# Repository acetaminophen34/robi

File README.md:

# Robi Development Project

ロボット「ロビ」の制御システムを開発・実験するためのプロジェクトです。

ESP32を用いたサーボモーター制御、Pythonによる操作GUI・モーション編集、Jetsonを用いた認識処理、制御基板の設計などを扱います。

## 使い方を探す

| やりたいこと | 案内 |
|---|---|
| ロビと対話し、モーションを実行する | [Jetson実機環境・起動方法](jetson/README.md) |
| ロビとテキストで会話する | [LLM対話の環境・起動方法](jetson/llm/README.md#起動) |
| どのプログラムを使うか確認する | [LLMファイルの役割](jetson/llm/README.md#ファイルの役割) |
| 口調・返答・モーション選択を調整する | [LLM対話の設定](jetson/llm/README.md#設定) |
| 起動や推論のエラーを調べる | [困ったとき](jetson/llm/README.md#困ったとき) |
| Jetsonへコードを反映する | [GitHub経由](jetson/llm/README.md#github経由のデプロイ)・[SSH/SCP経由](jetson/llm/README.md#macからsshscpで今回の差分を試す) |
| モーションを編集・再生する | [モーションエディタの使い方](motion_editor/README.md) |
| JetsonからUSB経由でRobiに接続する | [ESP32とのシリアル接続メモ](jetson/serial_connection.md) |
| Jetsonの推論環境を準備する | [jetson-labの環境構築](https://github.com/acetaminophen34/jetson-lab)・[llama-serverの追加ビルド](https://github.com/acetaminophen34/jetson-lab/blob/main/llama-cpp/server.md) |

Jetsonでの対話＋モーション制御は[実機環境・起動方法](jetson/README.md)を参照してください。テキスト対話のみの場合は`jetson/llm/chat.py`から起動します。サーバーの導入・ビルドはjetson-lab、対話の使い方・設定はこのリポジトリで管理しています。

## ディレクトリ構成

| ディレクトリ | 内容 |
|---|---|
| `esp/` | ESP32向けプログラムおよびPython GUI |
| `esp/gui_motion/` | モーション編集・制御の試作とテスト |
| `esp/head/` | 頭部のサーボ・LEDなどの制御 |
| `esp/servo/` | サーボモーターの動作確認 |
| `motion_editor/` | モーション作成・編集・再生用のPythonツール |
| `jetson/llm/` | Qwen3常駐サーバーによるテキスト対話・モーション選択（[手順](jetson/llm/README.md)） |
| `jetson/classification/` | Jetson向けの分類処理 |
| `robi_PCB/` | KiCadによる制御基板の設計データ |

## 開発環境

使用する技術・ツール：

- Python
- Arduino / ESP32
- NVIDIA Jetson
- KiCad
- Visual Studio Code

Pythonプログラムの依存パッケージは、各ディレクトリの`requirements.txt`を参照してください。

## モーションデータ

モーションはJSON形式で管理しています。

`motion_editor/motions/`にモーションデータを配置し、編集・再生ツールから利用します。

データ形式や操作方法の詳細は、各ツールのREADMEを参照してください。

## Git管理について

本リポジトリでは、開発用のソースコード・設定ファイル・基板設計データを管理します。

仮想環境、ビルド生成物、一時ファイル、KiCadの自動バックアップなどは原則として管理対象外です。

また、一部の既存ソフトウェア・関連データは権利関係の確認が必要なため、本リポジトリには含めていません。

## 開発状況

開発・実験中のプロジェクトです。各機能の仕様や構成は変更される場合があります。

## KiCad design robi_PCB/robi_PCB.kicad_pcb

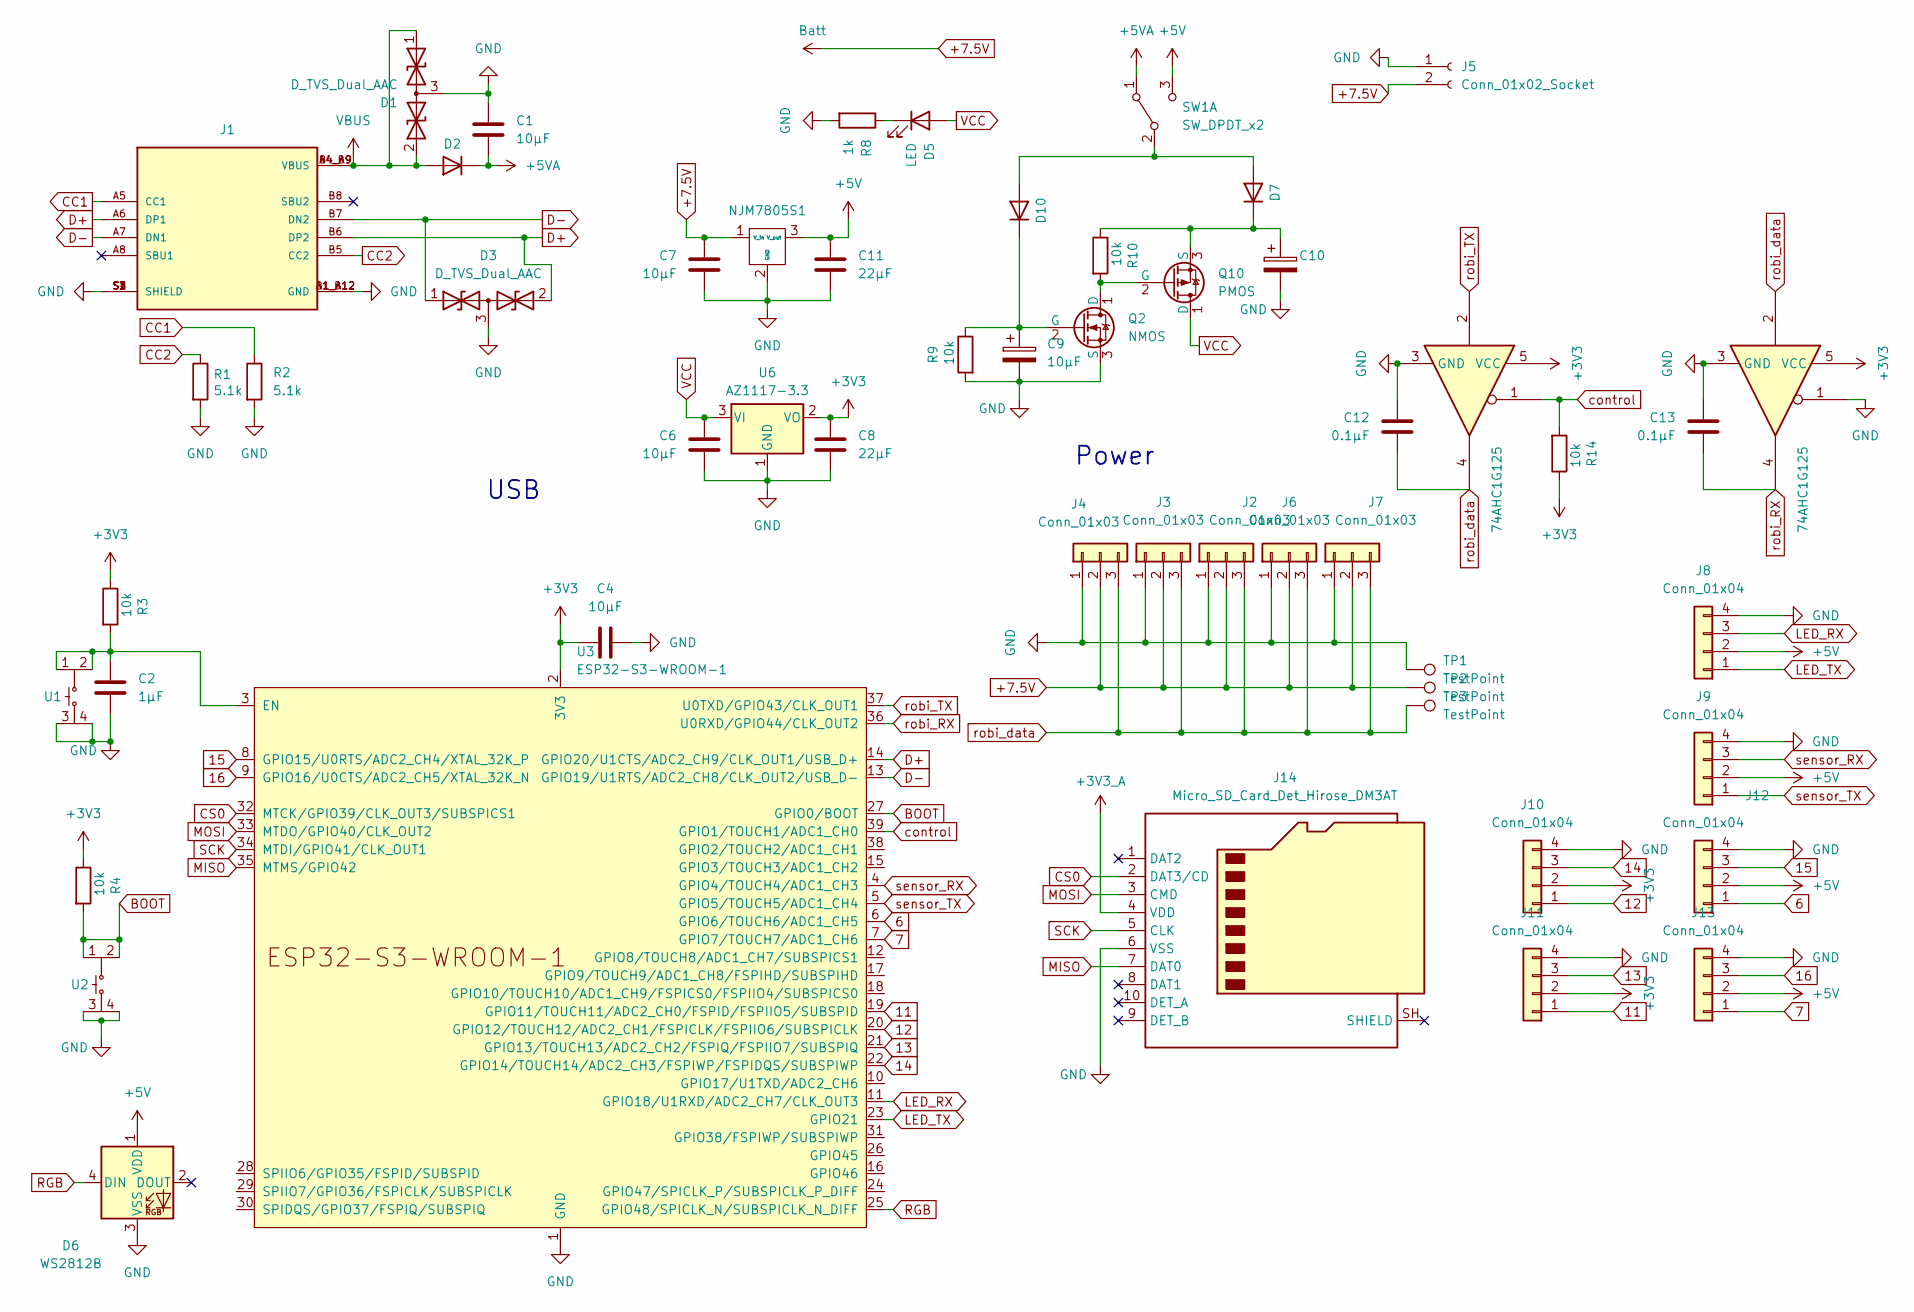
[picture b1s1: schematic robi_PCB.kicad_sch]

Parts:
C1, C4, C6, C7: 10μF; C_0805_2012Metric
C2: 1μF; C_0603_1608Metric
C8, C11: 22μF; C_0805_2012Metric
C9: 10μF; C_1206_3216Metric
C10: C_Polarized; CP_Radial_D8.0mm_P3.50mm
C12, C13: 0.1μF; C_0805_2012Metric
D1, D3: D_TVS_Dual_AAC; SOT-23
D2, D7, D10: D; D_SOD-323_HandSoldering
D5: LED; LED_0603_1608Metric
D6: WS2812B; LED_WS2812B_PLCC4_5.0x5.0mm_P3.2mm
J1: 5077CR-16SMC2-BK-TR; USB-C_SMT; PARTREV B
J2, J3, J4, J6, J7: Conn_01x03; JST_PH_B3B-PH-K_1x03_P2.00mm_Vertical
J5: Conn_01x02_Socket; JST_XH_B2B-XH-A_1x02_P2.50mm_Vertical
J8: Conn_01x04; JST_PH_B4B-PH-K_1x04_P2.00mm_Vertical
J9, J10, J11, J12, J13: Conn_01x04; PinHeader_1x04_P2.54mm_Vertical
J14: Micro_SD_Card_Det_Hirose_DM3AT; microSD_HC_Hirose_DM3AT-SF-PEJM5
NJM7805S1: NJM7805SDL1
Q2: NMOS; NMOS_IRLML6344TRPBFTR
Q10: PMOS; PMOS_AO3401A
R1, R2: 5.1k; R_0805_2012Metric
R3, R4, R9, R10, R14: 10k; R_0805_2012Metric
R8: 1k; R_0805_2012Metric
SW1: SW_DPDT_x2; SS-12D00G3
TP1, TP2, TP3: TestPoint; TestPoint_THTPad_1.0x1.0mm_Drill0.5mm
U1, U2: SKRPABE010
U3: ESP32-S3-WROOM-1
U4, U5: 74AHC1G125; SOT-23-5
U6: AZ1117-3.3; SOT-223-3_TabPin2

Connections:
6: J12.1, U3.6 (GPIO6/TOUCH6/ADC1_CH5)
7: J13.1, U3.7 (GPIO7/TOUCH7/ADC1_CH6)
11: J11.1, U3.19 (GPIO11/TOUCH11/ADC2_CH0/FSPID/FSPIIO5/S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)
12: J10.1, U3.20 (GPIO12/TOUCH12/ADC2_CH1/FSPICLK/FSPIIO6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)
13: J11.3, U3.21 (GPIO13/TOUCH13/ADC2_CH2/FSPIQ/FSPIIO7/S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)
14: J10.3, U3.22 (GPIO14/TOUCH14/ADC2_CH3/FSPIWP/FSPIDQS/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)
15: J12.3, U3.8 (GPIO15/U0RTS/ADC2_CH4/XTAL_32K_P)
16: J13.3, U3.9 (GPIO16/U0CTS/ADC2_CH5/XTAL_32K_N)
+3V3: C4.1, C8.1, J10.2, J11.2, R3.1, R4.1, R14.1, U3.2 (3V3), U4.5 (VCC), U5.5 (VCC), U6.2 (VO)
+3V3_A: J14.4 (VDD)
+5V: C11.1, D6.1 (VDD), J8.2, J9.2, J12.2, J13.2, NJM7805S1.3 (V_out), SW1.3 (C)
+5VA: C1.2, D2.1 (K), SW1.1 (A)
+7.5V: C7.1, J2.2, J3.2, J4.2, J5.2, J6.2, J7.2, NJM7805S1.1 (V_in), TP2.1 (1_1)
BOOT: R4.2, U2.1, U2.2, U3.27 (GPIO0/BOOT)
CC1: J1.A5 (CC1), R2.1
CC2: J1.B5 (CC2), R1.1
CS0: J14.2 (DAT3/CD), U3.32 (MTCK/GPIO39/CLK_OUT3/SUBSPICS1)
D+: D3.2 (A2), J1.A6 (DP1), J1.B6 (DP2), U3.14 (GPIO20/U1CTS/ADC2_CH9/CLK_OUT1/USB_D+)
D-: D3.1 (A1), J1.A7 (DN1), J1.B7 (DN2), U3.13 (GPIO19/U1RTS/ADC2_CH8/CLK_OUT2/USB_D-)
GND: C1.1, C2.2, C4.2, C6.2, C7.2, C8.2, C9.2, C10.2, C11.2, C12.1, C13.1, D1.3 (common), D3.3 (common), D6.3 (VSS), J1.A1_B12 (GND), J1.B1_A12 (GND), J1.S1 (SHIELD), J1.S2 (SHIELD), J1.S3 (SHIELD), J1.S4 (SHIELD), J2.1, J3.1, J4.1, J5.1, J6.1, J7.1, J8.4, J9.4, J10.4, J11.4, J12.4, J13.4, J14.6 (VSS), NJM7805S1.2 (GND), Q2.3 (S), R1.2, R2.2, R8.2, R9.2, TP1.1 (1_1), U1.3, U1.4, U2.3, U2.4, U3.1 (GND), U3.40 (GND), U3.41 (GND), U4.3 (GND), U5.1, U5.3 (GND), U6.1 (GND)
LED_RX: J8.3, U3.11 (GPIO18/U1RXD/ADC2_CH7/CLK_OUT3)
LED_TX: J8.1, U3.23 (GPIO21)
MISO: J14.7 (DAT0), U3.35 (MTMS/GPIO42)
MOSI: J14.3 (CMD), U3.33 (MTDO/GPIO40/CLK_OUT2)
unnamed: D5.1 (K), R8.1
unnamed: C10.1, D7.1 (K), Q10.3 (S), R10.1
unnamed: D7.2 (A), D10.2 (A), SW1.2 (B)
unnamed: C9.1, D10.1 (K), Q2.2 (G), R9.1
unnamed: Q2.1 (D), Q10.2 (G), R10.2
unnamed: C2.1, R3.2, U1.1, U1.2, U3.3 (EN)
RGB: D6.4 (DIN), U3.25 (GPIO48/SPICLK_N/SUBSPICLK_N_DIFF)
SCK: J14.5 (CLK), U3.34 (MTDI/GPIO41/CLK_OUT1)
VBUS: D1.1 (A1), D1.2 (A2), D2.2 (A), J1.A4_B9 (VBUS), J1.B4_A9 (VBUS)
VCC: C6.1, D5.2 (A), Q10.1 (D), U6.3 (VI)
control: R14.2, U3.39 (GPIO1/TOUCH1/ADC1_CH0), U4.1
robi_RX: C13.2, U3.36 (U0RXD/GPIO44/CLK_OUT2), U5.4
robi_TX: U3.37 (U0TXD/GPIO43/CLK_OUT1), U4.2
robi_data: C12.2, J2.3, J3.3, J4.3, J6.3, J7.3, TP3.1 (1_1), U4.4, U5.2
sensor_RX: J9.3, U3.4 (GPIO4/TOUCH4/ADC1_CH3)
sensor_TX: J9.1, U3.5 (GPIO5/TOUCH5/ADC1_CH4)

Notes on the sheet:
USB
Power

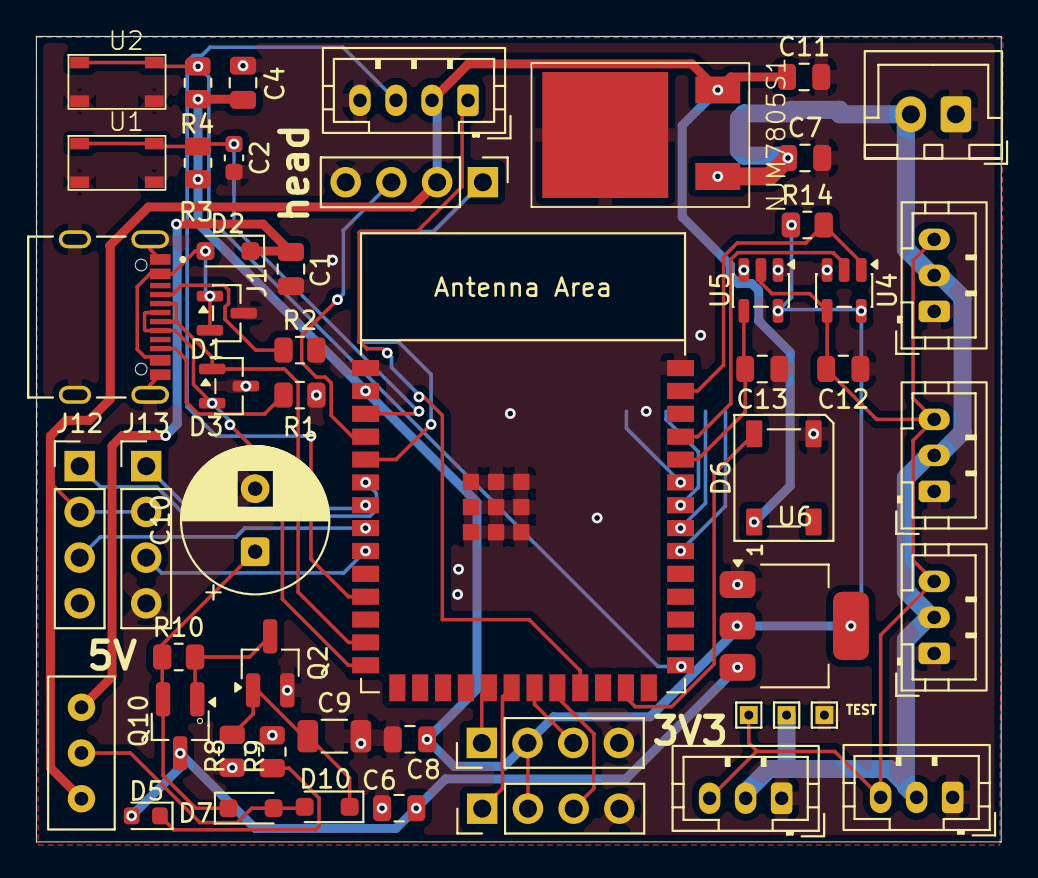
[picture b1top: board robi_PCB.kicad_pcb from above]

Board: 2 copper layers, 53.6 x 44.8 mm, 53 parts (1 on the bottom side), 39 nets.

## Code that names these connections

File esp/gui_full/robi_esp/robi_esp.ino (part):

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static const uint32_t SERVO_BAUD = 115200;

// ---------- LED UART ----------
static const int LED_TX_PIN = 17;
static const int LED_RX_PIN = 18;

// ---------- Sensor UART ----------
static const int SENSOR_TX_PIN = 5;
static const int SENSOR_RX_PIN = 4;

// ---------- microSD SPI ----------
static const int SD_CS_PIN   = 39;
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
// ============================================================
// LED: legacy I2C head board (same protocol as LED_gui.ino).
// GPIO42/41 are shared with the unused SD pin definitions above.
// ============================================================

static const int LED_SDA_PIN = 42;
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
